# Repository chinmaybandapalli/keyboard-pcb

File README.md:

# keyboard-pcb
A keyboard PCB designed to use Cherry MX switches. WORK IN PROGRESS, check https://chinmaybandapalli.github.io/projects/ for some more documentation.

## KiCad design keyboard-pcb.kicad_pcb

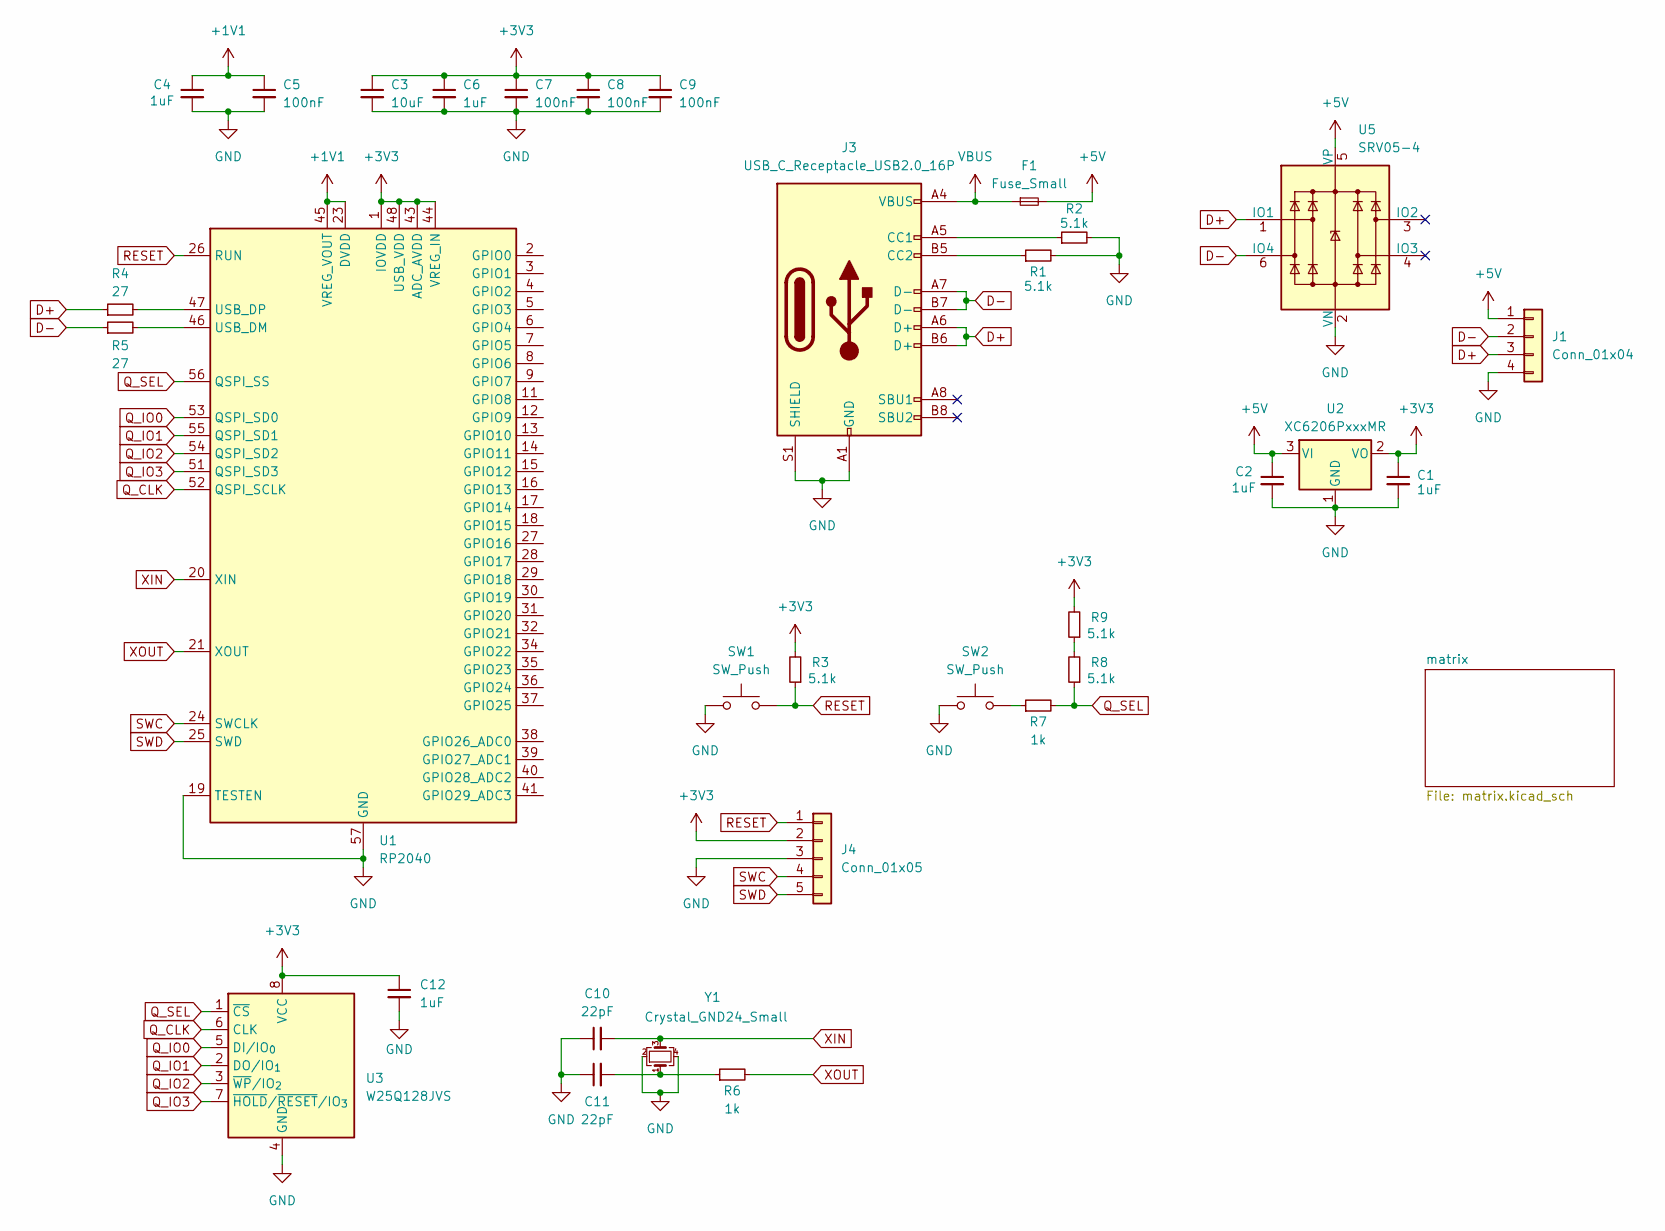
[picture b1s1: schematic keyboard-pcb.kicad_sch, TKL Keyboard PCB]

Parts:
C1, C2, C4, C6, C12: 1uF; C_0805_2012Metric
C3: 10uF; C_0805_2012Metric
C5, C7, C8, C9: 100nF; C_0805_2012Metric
C10, C11: 22pF; C_0805_2012Metric
F1: Fuse_Small; Fuse_1206_3216Metric
J1: Conn_01x04; JST_SH_SM04B-SRSS-TB_1x04-1MP_P1.00mm_Horizontal
J3: USB_C_Receptacle_USB2.0_16P; USB_C_Receptacle_HRO_TYPE-C-31-M-12
J4: Conn_01x05; PinHeader_1x05_P2.54mm_Vertical
R1, R2, R3, R8, R9: 5.1k; R_0805_2012Metric
R4, R5: 27; R_0805_2012Metric
R6, R7: 1k; R_0805_2012Metric
SW1, SW2: SW_Push; SW_SPST_TL3342
U1: RP2040; QFN-56-1EP_7x7mm_P0.4mm_EP3.2x3.2mm
U2: XC6206PxxxMR; SOT-23-3
U3: W25Q128JVS; SOIC-8_5.3x5.3mm_P1.27mm
U5: SRV05-4; SOT-23-6-routable
Y1: Crystal_GND24_Small; Crystal_SMD_3225-4Pin_3.2x2.5mm

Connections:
+1V1: C4.1, C5.1, U1.23 (DVDD), U1.45 (VREG_VOUT), U1.50 (DVDD); also elsewhere on the board
+3V3: C1.1, C3.1, C6.1, C7.1, C8.1, C9.1, C12.1, J4.2, R3.2, R9.2, U1.1 (IOVDD), U1.10 (IOVDD), U1.22 (IOVDD), U1.33 (IOVDD), U1.42 (IOVDD), U1.43 (ADC_AVDD), U1.44 (VREG_IN), U1.48 (USB_VDD), U1.49 (IOVDD), U2.2 (VO), U3.8 (VCC); also elsewhere on the board
+5V: C2.1, F1.2, J1.1, U2.3 (VI), U5.5 (VP)
D+: J1.3, J3.A6 (D+), J3.B6 (D+), R4.1, U5.1 (IO1)
D-: J1.2, J3.A7 (D-), J3.B7 (D-), R5.1, U5.6 (IO4)
GND: C1.2, C2.2, C3.2, C4.2, C5.2, C6.2, C7.2, C8.2, C9.2, C10.1, C11.1, C12.2, J1.4, J3.A1 (GND), J3.A12 (GND), J3.B1 (GND), J3.B12 (GND), J3.S1 (SHIELD), J4.3, R1.2, R2.2, SW1.1, SW2.1, U1.19 (TESTEN), U1.57 (GND), U2.1 (GND), U3.4 (GND), U5.2 (VN), Y1.2, Y1.4; also elsewhere on the board
unnamed 6: R7.1, SW2.2; also elsewhere on the board
unnamed: C11.2, R6.1, Y1.1
unnamed: J3.A5 (CC1), R2.1
unnamed: J3.B5 (CC2), R1.1
unnamed: R8.2, R9.1
unnamed: R5.2, U1.46 (USB_DM)
unnamed: R4.2, U1.47 (USB_DP)
Q_CLK: U1.52 (QSPI_SCLK), U3.6 (CLK)
Q_IO0: U1.53 (QSPI_SD0), U3.5 (DI/IO_{0})
Q_IO1: U1.55 (QSPI_SD1), U3.2 (DO/IO_{1})
Q_IO2: U1.54 (QSPI_SD2), U3.3 (~WP/IO_{2})
Q_IO3: U1.51 (QSPI_SD3), U3.7 (~HOLD/~RESET/IO_{3})
Q_SEL: R7.2, R8.1, U1.56 (QSPI_SS), U3.1 (~CS)
RESET: J4.1, R3.1, SW1.2, U1.26 (RUN)
SWC: J4.4, U1.24 (SWCLK)
SWD: J4.5, U1.25 (SWD)
VBUS: F1.1, J3.A4 (VBUS), J3.A9 (VBUS), J3.B4 (VBUS), J3.B9 (VBUS)
XIN: C10.2, U1.20 (XIN), Y1.3
XOUT: R6.2, U1.21 (XOUT)

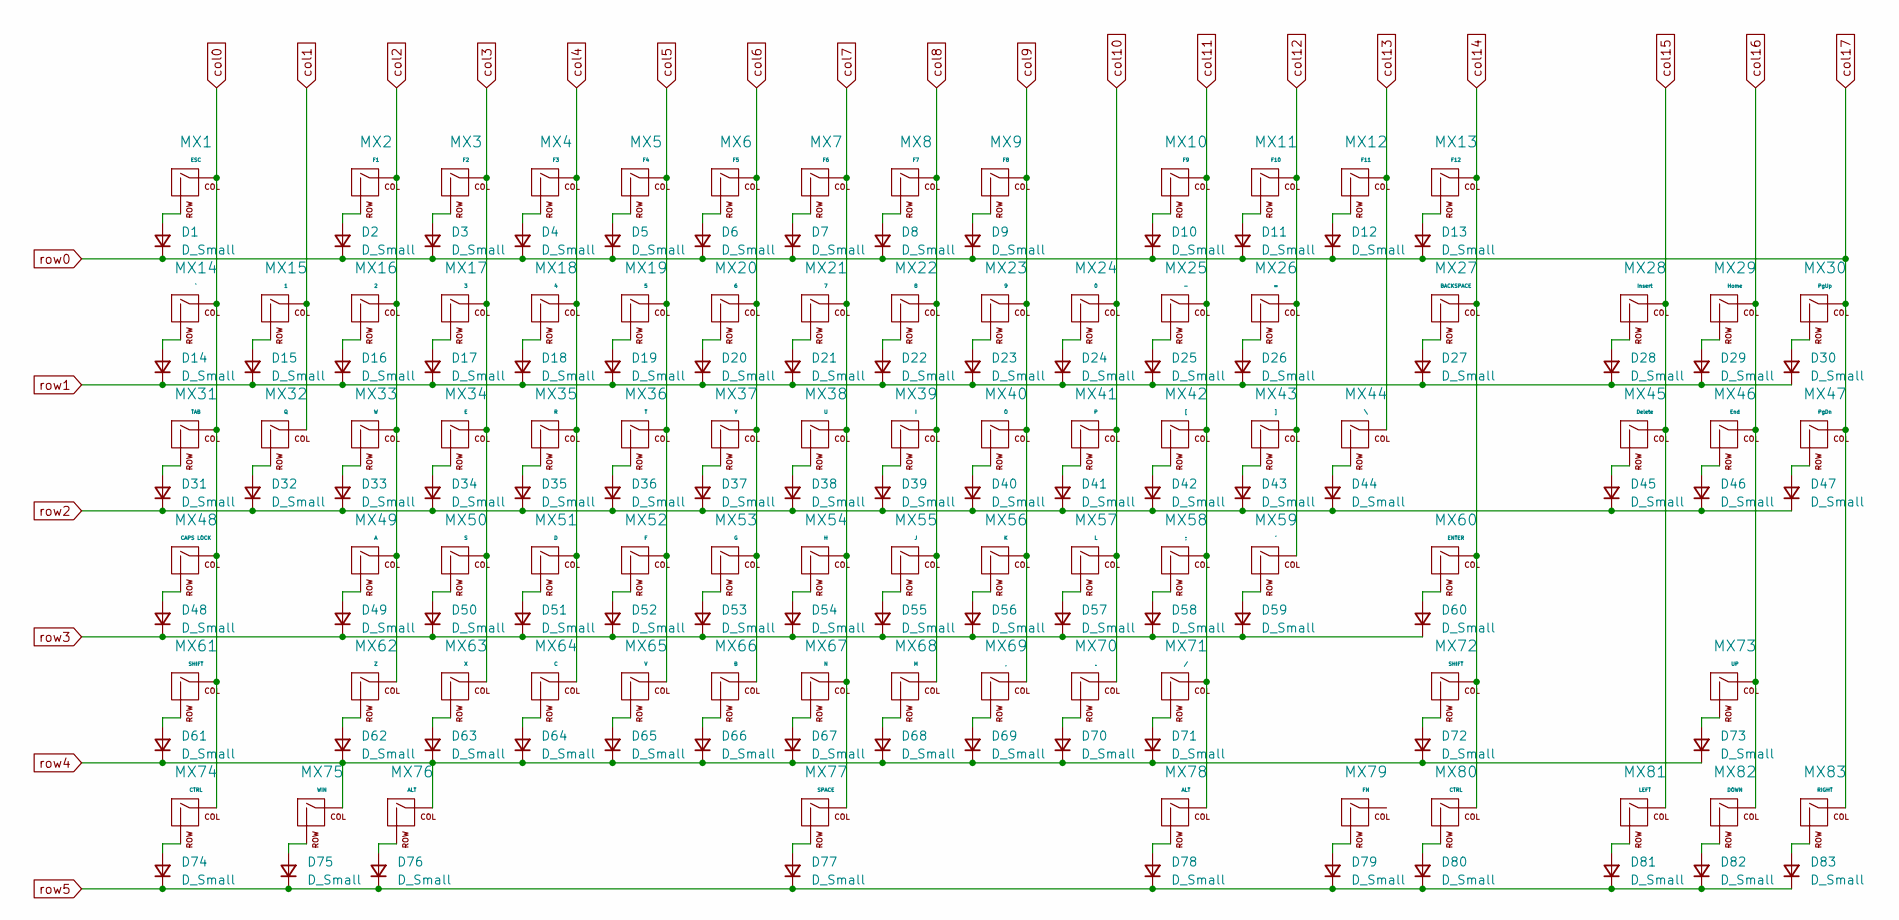
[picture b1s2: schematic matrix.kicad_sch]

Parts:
D1, D2, D3, D4, D5, D6, D7, D8, D9, D10, D11, D12, D13, D14, D15, D16, D17, D18, D19, D20, D21, D22, D23, D24, D25, D26, D27, D28, D29, D30, D31, D32, D33, D34, D35, D36, D37, D38, D39, D40, D41, D42, D43, D44, D45, D46, D47, D48, D49, D50, D51, D52, D53, D54, D55, D56, D57, D58, D59, D60, D61, D62, D63, D64, D65, D66, D67, D68, D69, D70, D71, D72, D73, D74, D75, D76, D77, D78, D79, D80, D81, D82, D83: D_Small; D_SOD-123
MX1: ESC; MX-Hotswap-1U
MX2: F1; MX-Hotswap-1U
MX3: F2; MX-Hotswap-1U
MX4: F3; MX-Hotswap-1U
MX5: F4; MX-Hotswap-1U
MX6: F5; MX-Hotswap-1U
MX7: F6; MX-Hotswap-1U
MX8: F7; MX-Hotswap-1U
MX9: F8; MX-Hotswap-1U
MX10: F9; MX-Hotswap-1U
MX11: F10; MX-Hotswap-1U
MX12: F11; MX-Hotswap-1U
MX13: F12; MX-Hotswap-1U
MX14: `; MX-Hotswap-1U
MX15: 1; MX-Hotswap-1U
MX16: 2; MX-Hotswap-1U
MX17: 3; MX-Hotswap-1U
MX18: 4; MX-Hotswap-1U
MX19: 5; MX-Hotswap-1U
MX20: 6; MX-Hotswap-1U
MX21: 7; MX-Hotswap-1U
MX22: 8; MX-Hotswap-1U
MX23: 9; MX-Hotswap-1U
MX24: 0; MX-Hotswap-1U
MX25: -; MX-Hotswap-1U
MX26: =; MX-Hotswap-1U
MX27: BACKSPACE; MX-Hotswap-2U
MX28: Insert; MX-Hotswap-1U
MX29: Home; MX-Hotswap-1U
MX30: PgUp; MX-Hotswap-1U
MX31: TAB; MX-Hotswap-1.5U
MX32: Q; MX-Hotswap-1U
MX33: W; MX-Hotswap-1U
MX34: E; MX-Hotswap-1U
MX35: R; MX-Hotswap-1U
MX36: T; MX-Hotswap-1U
MX37: Y; MX-Hotswap-1U
MX38: U; MX-Hotswap-1U
MX39: I; MX-Hotswap-1U
MX40: O; MX-Hotswap-1U
MX41: P; MX-Hotswap-1U
MX42: [; MX-Hotswap-1U
MX43: ]; MX-Hotswap-1U
MX44: \; MX-Hotswap-1.5U
MX45: Delete; MX-Hotswap-1U
MX46: End; MX-Hotswap-1U
MX47: PgDn; MX-Hotswap-1U
MX48: CAPS LOCK; MX-Hotswap-1.75U
MX49: A; MX-Hotswap-1U
MX50: S; MX-Hotswap-1U
MX51: D; MX-Hotswap-1U
MX52: F; MX-Hotswap-1U
MX53: G; MX-Hotswap-1U
MX54: H; MX-Hotswap-1U
MX55: J; MX-Hotswap-1U
MX56: K; MX-Hotswap-1U
MX57: L; MX-Hotswap-1U
MX58: ;; MX-Hotswap-1U
MX59: '; MX-Hotswap-1U
MX60: ENTER; MX-Hotswap-2.25U
MX61: SHIFT; MX-Hotswap-2.25U
MX62: Z; MX-Hotswap-1U
MX63: X; MX-Hotswap-1U
MX64: C; MX-Hotswap-1U
MX65: V; MX-Hotswap-1U
MX66: B; MX-Hotswap-1U
MX67: N; MX-Hotswap-1U
MX68: M; MX-Hotswap-1U
MX69: ,; MX-Hotswap-1U
MX70: .; MX-Hotswap-1U
MX71: /; MX-Hotswap-1U
MX72: SHIFT; MX-Hotswap-2.75U
MX73: UP; MX-Hotswap-1U
MX74, MX80: CTRL; MX-Hotswap-1.5U
MX75: WIN; MX-Hotswap-1U
MX76, MX78: ALT; MX-Hotswap-1.5U
MX77: SPACE; MX-Hotswap-7U
MX79: FN; MX-Hotswap-1U
MX81: LEFT; MX-Hotswap-1U
MX82: DOWN; MX-Hotswap-1U
MX83: RIGHT; MX-Hotswap-1U

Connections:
unnamed: D1.2 (A), MX1.2 (ROW)
unnamed: D2.2 (A), MX2.2 (ROW)
unnamed: D3.2 (A), MX3.2 (ROW)
unnamed: D4.2 (A), MX4.2 (ROW)
unnamed: D5.2 (A), MX5.2 (ROW)
unnamed: D6.2 (A), MX6.2 (ROW)
unnamed: D7.2 (A), MX7.2 (ROW)
unnamed: D8.2 (A), MX8.2 (ROW)
unnamed: D9.2 (A), MX9.2 (ROW)
unnamed: D10.2 (A), MX10.2 (ROW)
unnamed: D11.2 (A), MX11.2 (ROW)
unnamed: D12.2 (A), MX12.2 (ROW)
unnamed: D13.2 (A), MX13.2 (ROW)
unnamed: D14.2 (A), MX14.2 (ROW)
unnamed: D15.2 (A), MX15.2 (ROW)
unnamed: D16.2 (A), MX16.2 (ROW)
unnamed: D17.2 (A), MX17.2 (ROW)
unnamed: D18.2 (A), MX18.2 (ROW)
unnamed: D19.2 (A), MX19.2 (ROW)
unnamed: D20.2 (A), MX20.2 (ROW)
unnamed: D21.2 (A), MX21.2 (ROW)
unnamed: D22.2 (A), MX22.2 (ROW)
unnamed: D23.2 (A), MX23.2 (ROW)
unnamed: D24.2 (A), MX24.2 (ROW)
unnamed: D25.2 (A), MX25.2 (ROW)
unnamed: D26.2 (A), MX26.2 (ROW)
unnamed: D27.2 (A), MX27.2 (ROW)
unnamed: D28.2 (A), MX28.2 (ROW)
unnamed: D29.2 (A), MX29.2 (ROW)
unnamed: D30.2 (A), MX30.2 (ROW)
unnamed: D31.2 (A), MX31.2 (ROW)
unnamed: D32.2 (A), MX32.2 (ROW)
unnamed: D33.2 (A), MX33.2 (ROW)
unnamed: D34.2 (A), MX34.2 (ROW)
unnamed: D35.2 (A), MX35.2 (ROW)
unnamed: D36.2 (A), MX36.2 (ROW)
unnamed: D37.2 (A), MX37.2 (ROW)
unnamed: D38.2 (A), MX38.2 (ROW)
unnamed: D39.2 (A), MX39.2 (ROW)
unnamed: D40.2 (A), MX40.2 (ROW)
unnamed: D41.2 (A), MX41.2 (ROW)
unnamed: D42.2 (A), MX42.2 (ROW)
unnamed: D43.2 (A), MX43.2 (ROW)
unnamed: D44.2 (A), MX44.2 (ROW)
unnamed: D45.2 (A), MX45.2 (ROW)
unnamed: D46.2 (A), MX46.2 (ROW)
unnamed: D47.2 (A), MX47.2 (ROW)
unnamed: D48.2 (A), MX48.2 (ROW)
unnamed: D49.2 (A), MX49.2 (ROW)
unnamed: D50.2 (A), MX50.2 (ROW)
unnamed: D51.2 (A), MX51.2 (ROW)
unnamed: D52.2 (A), MX52.2 (ROW)
unnamed: D53.2 (A), MX53.2 (ROW)
unnamed: D54.2 (A), MX54.2 (ROW)
unnamed: D55.2 (A), MX55.2 (ROW)
unnamed: D56.2 (A), MX56.2 (ROW)
unnamed: D57.2 (A), MX57.2 (ROW)
unnamed: D58.2 (A), MX58.2 (ROW)
unnamed: D59.2 (A), MX59.2 (ROW)
unnamed: D60.2 (A), MX60.2 (ROW)
unnamed: D61.2 (A), MX61.2 (ROW)
unnamed: D62.2 (A), MX62.2 (ROW)
unnamed: D63.2 (A), MX63.2 (ROW)
unnamed: D64.2 (A), MX64.2 (ROW)
unnamed: D65.2 (A), MX65.2 (ROW)
unnamed: D66.2 (A), MX66.2 (ROW)
unnamed: D67.2 (A), MX67.2 (ROW)
unnamed: D68.2 (A), MX68.2 (ROW)
unnamed: D69.2 (A), MX69.2 (ROW)
unnamed: D70.2 (A), MX70.2 (ROW)
unnamed: D71.2 (A), MX71.2 (ROW)
unnamed: D72.2 (A), MX72.2 (ROW)
unnamed: D73.2 (A), MX73.2 (ROW)
unnamed: D74.2 (A), MX74.2 (ROW)
unnamed: D75.2 (A), MX75.2 (ROW)
unnamed: D76.2 (A), MX76.2 (ROW)
unnamed: D77.2 (A), MX77.2 (ROW)
unnamed: D78.2 (A), MX78.2 (ROW)
unnamed: D79.2 (A), MX79.2 (ROW)
unnamed: D80.2 (A), MX80.2 (ROW)
unnamed: D81.2 (A), MX81.2 (ROW)
unnamed: D82.2 (A), MX82.2 (ROW)
unnamed: D83.2 (A), MX83.2 (ROW)
col0: MX1.1 (COL), MX14.1 (COL), MX31.1 (COL), MX48.1 (COL), MX61.1 (COL), MX74.1 (COL)
col1: MX15.1 (COL), MX32.1 (COL)
col2: MX2.1 (COL), MX16.1 (COL), MX33.1 (COL), MX49.1 (COL), MX62.1 (COL)
col3: MX3.1 (COL), MX17.1 (COL), MX34.1 (COL), MX50.1 (COL), MX63.1 (COL)
col4: MX4.1 (COL), MX18.1 (COL), MX35.1 (COL), MX51.1 (COL), MX64.1 (COL)
col5: MX5.1 (COL), MX19.1 (COL), MX36.1 (COL), MX52.1 (COL), MX65.1 (COL)
col6: MX6.1 (COL), MX20.1 (COL), MX37.1 (COL), MX53.1 (COL), MX66.1 (COL)
col7: MX7.1 (COL), MX21.1 (COL), MX38.1 (COL), MX54.1 (COL), MX67.1 (COL), MX77.1 (COL)
col8: MX8.1 (COL), MX22.1 (COL), MX39.1 (COL), MX55.1 (COL), MX68.1 (COL)
col9: MX9.1 (COL), MX23.1 (COL), MX40.1 (COL), MX56.1 (COL), MX69.1 (COL)
col10: MX24.1 (COL), MX41.1 (COL), MX57.1 (COL), MX70.1 (COL)
col11: MX10.1 (COL), MX25.1 (COL), MX42.1 (COL), MX58.1 (COL), MX71.1 (COL), MX78.1 (COL)
col12: MX11.1 (COL), MX26.1 (COL), MX43.1 (COL), MX59.1 (COL)
col13: MX12.1 (COL), MX44.1 (COL)
col14: MX13.1 (COL), MX27.1 (COL), MX60.1 (COL), MX72.1 (COL), MX80.1 (COL)
col15: MX28.1 (COL), MX45.1 (COL), MX81.1 (COL)
col16: MX29.1 (COL), MX46.1 (COL), MX73.1 (COL), MX82.1 (COL)
row1: D14.1 (K), D15.1 (K), D16.1 (K), D17.1 (K), D18.1 (K), D19.1 (K), D20.1 (K), D21.1 (K), D22.1 (K), D23.1 (K), D24.1 (K), D25.1 (K), D26.1 (K), D27.1 (K), D28.1 (K), D29.1 (K), D30.1 (K)
row2: D31.1 (K), D32.1 (K), D33.1 (K), D34.1 (K), D35.1 (K), D36.1 (K), D37.1 (K), D38.1 (K), D39.1 (K), D40.1 (K), D41.1 (K), D42.1 (K), D43.1 (K), D44.1 (K), D45.1 (K), D46.1 (K), D47.1 (K)
row3: D48.1 (K), D49.1 (K), D50.1 (K), D51.1 (K), D52.1 (K), D53.1 (K), D54.1 (K), D55.1 (K), D56.1 (K), D57.1 (K), D58.1 (K), D59.1 (K), D60.1 (K)
row4: D61.1 (K), D62.1 (K), D63.1 (K), D64.1 (K), D65.1 (K), D66.1 (K), D67.1 (K), D68.1 (K), D69.1 (K), D70.1 (K), D71.1 (K), D72.1 (K), D73.1 (K), MX75.1 (COL), MX76.1 (COL)
row5: D74.1 (K), D75.1 (K), D76.1 (K), D77.1 (K), D78.1 (K), D79.1 (K), D80.1 (K), D81.1 (K), D82.1 (K), D83.1 (K)

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
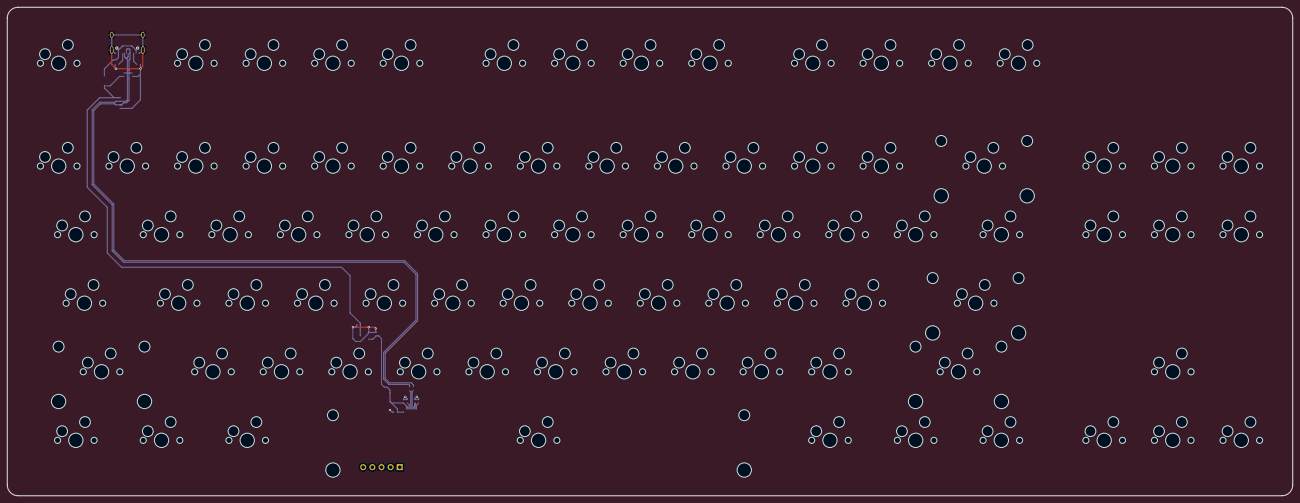
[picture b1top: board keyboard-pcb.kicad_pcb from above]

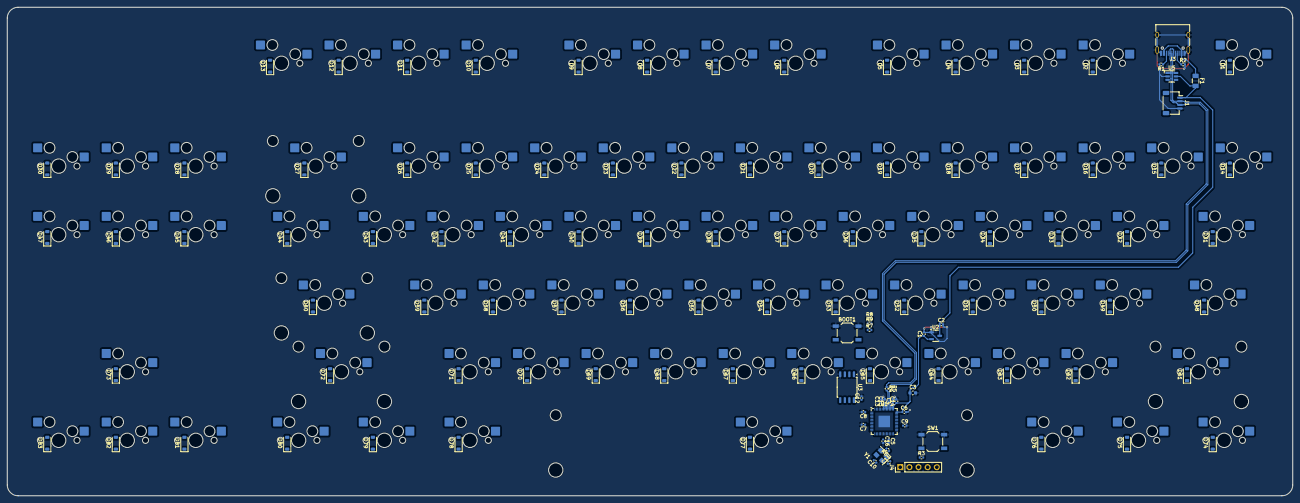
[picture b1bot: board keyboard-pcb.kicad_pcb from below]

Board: 2 copper layers, 357.2 x 135.7 mm, 202 parts (202 on the bottom side), 132 nets.

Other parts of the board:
BOOT1: SW_Push; SW_SPST_TL3342
C13, C14, C15, C16: 100nF; C_0402_1005Metric

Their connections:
+1V1: C13.1; also elsewhere on the board
+3V3: C14.1, C15.1, C16.1; also elsewhere on the board
GND: BOOT1.1, C13.2, C14.2, C15.2, C16.2; also elsewhere on the board
unnamed 6: BOOT1.2; also elsewhere on the board

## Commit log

2025-07-02 Initialize project
    3 new KiCAD files
2025-07-02 Add submodules
2025-07-02 Add footprint libraries
2025-07-05 Added footprint libraries
2025-07-05 Progressed microcontroller design
    Atmega32u4 schematic work
2025-07-05 Progressed microcontroller design
2025-07-05 Moved keyboard backups to another spot
2025-07-05 Removed design-block-lib-table
    Unnecessary file
2025-07-08 Completed USB Connector
    Wired USB C connector with fuse and ESD protection
2025-07-12 Constructed TKL keyswitch matrix
    An 87 MX switch matrix with diodes
2025-07-16 Changed MCU circuitry
    Atmega32u4 -> rp2040, updated USB-C connector, updated ESD protection, added memory chip, added voltage regulator
    Tutorial followed: https://youtu.be/6Z49bynRqj8?si=SZUICHd2tr064eZg
2025-07-18 Assigned footprints to components
    Also edited layout slightly (7u spacebar and removal of PrtSc, ScLk, Pause)
2025-07-18 Adjusted settings
2025-07-18 Edited PCB layout
    Put all MX switches in TKL format
2025-07-18 Removed backup folder
    Not needed for GitHub repo
2025-07-19 Wired components of PCB
    Type-C 2.0 Connector system
2025-07-20 Wired MCU loop on PCB
    All components of MCU loop wired together, keyswitch matrix remaining
